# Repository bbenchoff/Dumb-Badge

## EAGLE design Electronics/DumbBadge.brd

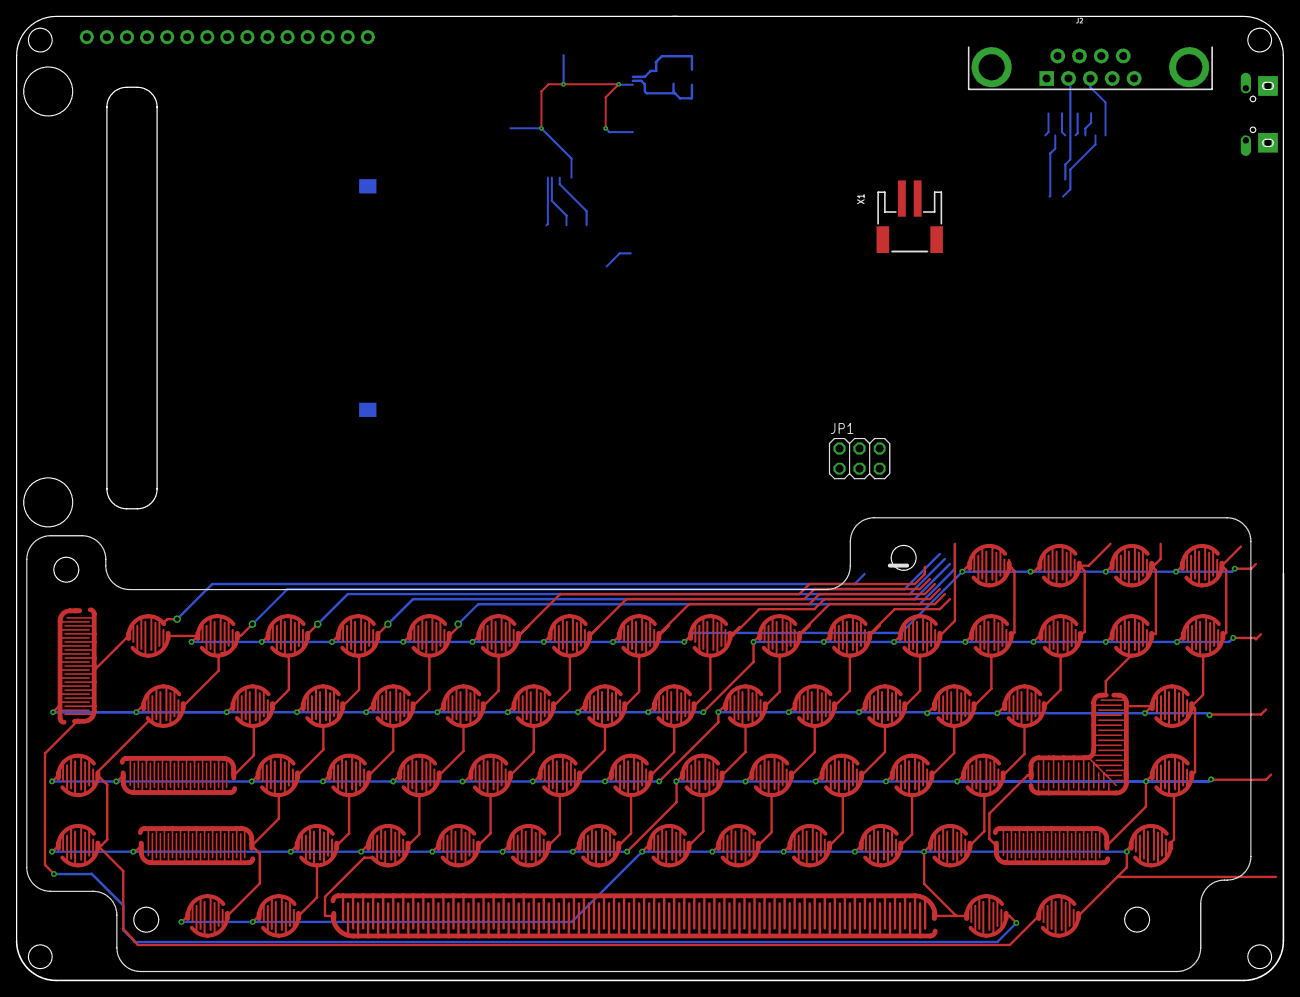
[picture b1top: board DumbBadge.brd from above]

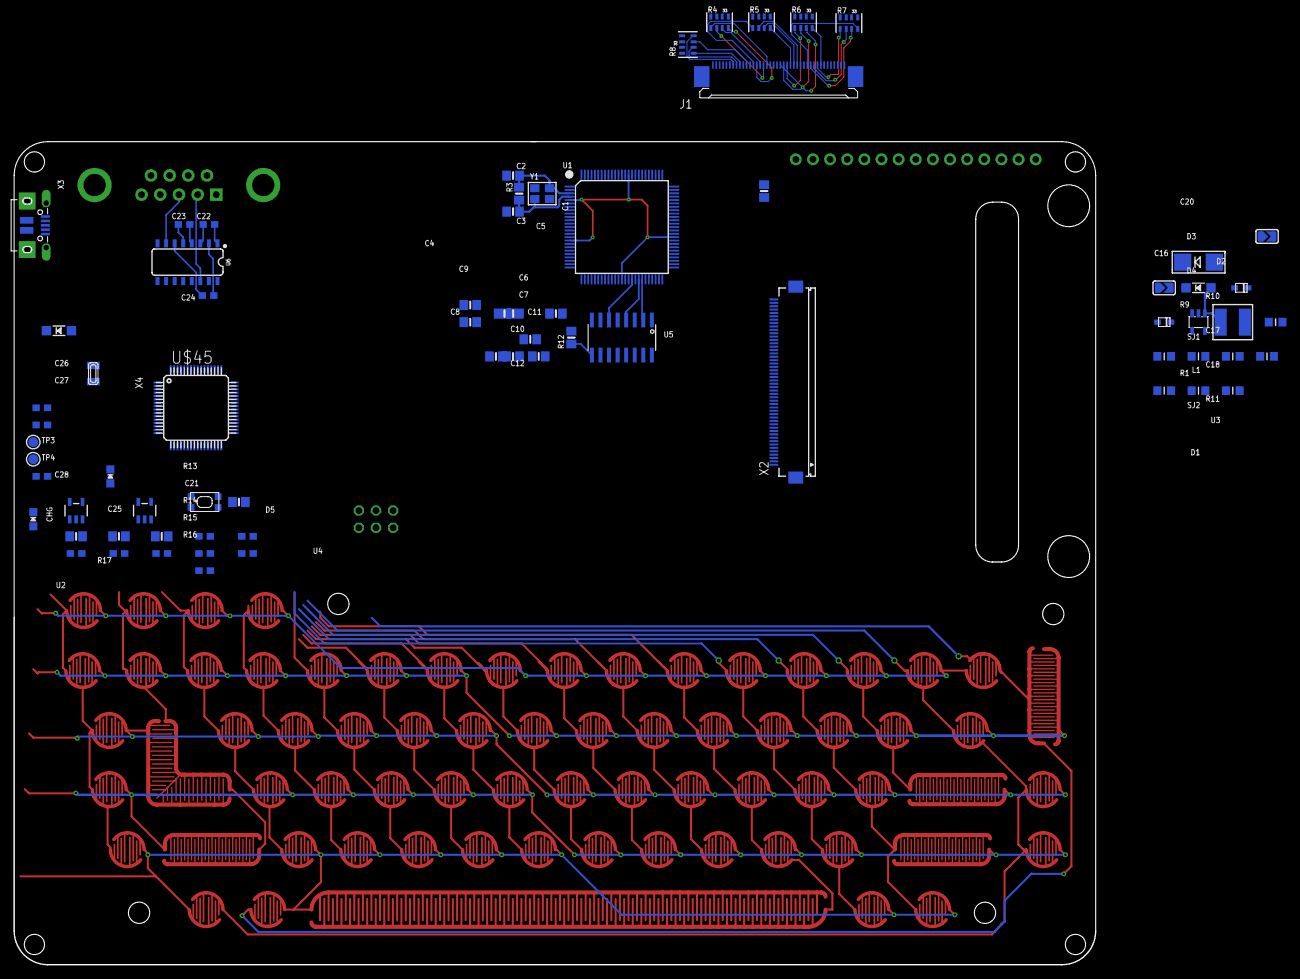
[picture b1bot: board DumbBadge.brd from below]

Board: 2 copper layers, 160.3 x 122.0 mm, 143 parts (70 on the bottom side), 115 nets.

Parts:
C1, C4, C5, C6, C7, C8, C9, C10, C11, C12: 0.1uF; 0805-NO
C2, C3: 20pF; 0805-NO
C13, C15, C21: 10µF; 0805-NO
C14, C19, C28: 1uF; 0603-NO
C16: 10uF; _0805MP
C17, C20: 1uF; _0805MP
C18: 0.1uF; _0805MP
C22, C23, C24: 0.1uF; 0603-NO
C25: 10uF; 0805-NO
C26, C27: 22pF; 0603-NO
CHG: ORANGE; CHIPLED_0805_NOOUTLINE
D1: MM3Z24VT1G; SMADIODE
D2: MBR0540; SOD-123
D3, D4: 1N4148; SOD-323F
D5: MBR120; SOD-123
J1: 40PINFPCM4-1734839-0; 4-1734839-0
J2: DB9
JP1: 2X03
JP2: Breakout; 1X15-CB
K-1, K-2, K-5: 1U_PAD; SILICONE_SWITCH
K_0, K_3, K_4, K_6, K_7, K_8, K_9: 1U_PAD; SILICONE_SWITCH
K_<: 1U_PAD; SILICONE_SWITCH
K_>: 1U_PAD; SILICONE_SWITCH
K_?: 1U_PAD; SILICONE_SWITCH
K_A: 1U_PAD; SILICONE_SWITCH
K_B: 1U_PAD; SILICONE_SWITCH
K_BACK: 1U_PAD; SILICONE_SWITCH
K_BREAK: 1U_PAD; SILICONE_SWITCH
K_C: 1U_PAD; SILICONE_SWITCH
K_CAPS: 1U_PAD; SILICONE_SWITCH
K_CONTROL: 2U_PAD; SILICONE_SWITCH_2U
K_D: 1U_PAD; SILICONE_SWITCH
K_DEL: 1U_PAD; SILICONE_SWITCH
K_DOWN: 1U_PAD; SILICONE_SWITCH
K_E: 1U_PAD; SILICONE_SWITCH
K_ESC: 1U_PAD; SILICONE_SWITCH
K_F: 1U_PAD; SILICONE_SWITCH
K_G: 1U_PAD; SILICONE_SWITCH
K_H: 1U_PAD; SILICONE_SWITCH
K_I: 1U_PAD; SILICONE_SWITCH
K_J: 1U_PAD; SILICONE_SWITCH
K_K: 1U_PAD; SILICONE_SWITCH
K_L: 1U_PAD; SILICONE_SWITCH
K_LEFT: 1U_PAD; SILICONE_SWITCH
K_LEFTALT: 1U_PAD; SILICONE_SWITCH
K_LEFTMETA: 1U_PAD; SILICONE_SWITCH
K_LINE: 1U_PAD; SILICONE_SWITCH
K_LSHIFT: 2U_PAD; SILICONE_SWITCH_2U
K_M: 1U_PAD; SILICONE_SWITCH
K_N: 1U_PAD; SILICONE_SWITCH
K_NOSCL: 1U_PAD; SILICONE_SWITCH
K_O: 1U_PAD; SILICONE_SWITCH
K_P: 1U_PAD; SILICONE_SWITCH
K_PIPE: 1U_PAD; SILICONE_SWITCH
K_PLUS: 1U_PAD; SILICONE_SWITCH
K_Q: 1U_PAD; SILICONE_SWITCH
K_QUOTE: 1U_PAD; SILICONE_SWITCH
K_R: 1U_PAD; SILICONE_SWITCH
K_RETURN: RETURN_PAD; SILICONE_RETURN
K_RIGHT: 1U_PAD; SILICONE_SWITCH
K_RIGHTALT: 1U_PAD; SILICONE_SWITCH
K_RIGHTMETA: 1U_PAD; SILICONE_SWITCH
K_RSHIFT: 2U_PAD; SILICONE_SWITCH_2U
K_S: 1U_PAD; SILICONE_SWITCH
K_SEMI: 1U_PAD; SILICONE_SWITCH
K_SETUP: 2U_PAD; SILICONE_SWITCH_2U
K_SPACE: SPACE_PAD; SILICONE_SPACE
K_T: 1U_PAD; SILICONE_SWITCH
K_TAB: 1U_PAD; SILICONE_SWITCH
K_TILDE: 1U_PAD; SILICONE_SWITCH
K_U: 1U_PAD; SILICONE_SWITCH
K_UP: 1U_PAD; SILICONE_SWITCH
K_USCORE: 1U_PAD; SILICONE_SWITCH
K_V: 1U_PAD; SILICONE_SWITCH
K_W: 1U_PAD; SILICONE_SWITCH
K_X: 1U_PAD; SILICONE_SWITCH
K_Y: 1U_PAD; SILICONE_SWITCH
K_Z: 1U_PAD; SILICONE_SWITCH
K_{: 1U_PAD; SILICONE_SWITCH
K_}: 1U_PAD; SILICONE_SWITCH
L: RED; CHIPLED_0805_NOOUTLINE
L1: 6.8uH large inductor; INDUCTOR_5X5MM_NR5040_NOTHERMALS
R1: 3Ω; _0805MP
R2: 2.2K; 0603-NO
R3: 1M; 0805-NO
R4, R5, R6, R7, R8: 33; RESPACK_4X0603
R9, R10: 12Ω; _0805MP
R11: 10K; _0805MP
R12: 10K; 0805-NO
R13: 1K; 0603-NO
R14: 10K\; 0603-NO
R15, R17: 100k; 0603-NO
R16: 100K; 0603-NO
SJ1: +25mA; SOLDERJUMPER_ARROW_NOPASTE
SJ2: +100mA; SOLDERJUMPER_ARROW_NOPASTE
SW1: SPST_TACT-KMR2; KMR2
TP3, TP4: TESTPOINT_ROUND_1.5MM
U1: RA8875; LQFP100
U2: SPX3819-3.3; SOT23-5
U3: FAN5333BSX; SOT23-5@1
U4: MCP73831T-2ACI/OT; SOT23-5
U5: 74HC4050; SOIC16
U6: MAX3232; SO16
U$45: ATSAMD21J18A-AUT; TQFP64-10X10
X1: JSTPH; JSTPH2
X2: FH12-50S-0.5SH
X3: microUSB; 4UCONN_20329_V2
X4: 32.768; XTAL3215
Y1: 20MHz; CRYSTAL_3.2X2.5

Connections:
1: X2.13, X2.14, X2.15, X2.16, X2.17, X2.18, X2.19, X2.20, X2.21, X2.22, X2.23, X2.24, X2.25, X2.26, X2.27, X2.28, X2.29, X2.30, X2.31, X2.32, X2.33, X2.34, X2.35, X2.36
1.5V: C8.1, C9.1, C10.1, C12.1, U1.5, U1.17, U1.38, U1.60, U1.86
!RESET: SW1.1, SW1.3, U$45.52
+3V3: C4.1, C5.1, C6.1, C7.1, C11.1, C14.1, C15.1, C25.1, J1.4, JP2.13, R12.2, U1.2, U1.13, U1.25, U1.27, U1.40, U1.62, U1.76, U1.77, U1.78, U1.79, U1.80, U1.87, U2.5, U5.1, U$45.8, U$45.21, U$45.34, U$45.48, U$45.56
+24V: C17.1, C20.1, D1.C, D2.C, J1.2
AREF: C19.1, U$45.4
B3: J1.24, R4.5
B4: J1.25, R4.6
B5: J1.26, R4.7
B6: J1.27, R4.8
B7: J1.28, R5.5
CS: JP2.8, X2.42
D9: R15.2, R16.1, U$45.16
D13: R2.1, U$45.36
D+: U$45.46, X3.D+
D-: U$45.45, X3.D-
DE: J1.34, R8.8, X2.12
EN: R17.2, U2.3
G2: J1.15, R5.6
G3: J1.16, R5.7
G4: J1.17, R5.8
G5: J1.18, R6.5
G6: J1.19, R6.6
G7: J1.20, R6.7
GND: C1.2, C2.1, C3.1, C4.2, C5.2, C6.2, C7.2, C8.2, C9.2, C10.2, C11.2, C12.2, C13.2, C14.2, C15.2, C16.2, C17.2, C18.2, C19.2, C20.2, C21.2, C25.2, C26.2, C27.2, C28.2, J1.3, J1.5, J1.6, J1.7, J1.13, J1.14, J1.21, J1.22, J1.23, J1.29, J1.36, J2.5, JP2.14, L.C, R10.1, R14.2, R16.2, SJ1.1, SJ2.1, SW1.2, SW1.4, U1.1, U1.6, U1.10, U1.11, U1.12, U1.16, U1.23, U1.24, U1.26, U1.28, U1.33, U1.34, U1.35, U1.36, U1.37, U1.39, U1.45, U1.61, U1.70, U1.81, U1.85, U2.2, U3.2, U4.2, U5.8, U$45.7, U$45.22, U$45.33, U$45.47, U$45.54, X1.1, X2.45, X2.50, X3.BASE@1, X3.BASE@2, X3.GND, X3.SPRT@1, X3.SPRT@2, X3.SPRT@3, X3.SPRT@4
HSYNC: J1.32, R8.5, X2.10
INT: JP2.5, U1.8
KEYCOLUMN0: K_ESC.P$2, K_RIGHTALT.P$2, K_SETUP.P$2
KEYCOLUMN1: K-1.P$2, K_CAPS.P$2, K_NOSCL.P$2, K_RIGHTMETA.P$2, K_TAB.P$2
KEYCOLUMN2: K-2.P$2, K_CONTROL.P$2, K_Q.P$2
KEYCOLUMN3: K_3.P$2, K_A.P$2, K_LEFTMETA.P$2, K_LSHIFT.P$2, K_W.P$2
KEYCOLUMN4: K_4.P$2, K_E.P$2, K_LEFTALT.P$2, K_S.P$2, K_Z.P$2
KEYCOLUMN5: K-5.P$2, K_D.P$2, K_R.P$2, K_SPACE.P$1, K_X.P$2
KEYCOLUMN6: K_6.P$2, K_C.P$2, K_F.P$2, K_T.P$2
KEYCOLUMN7: K_7.P$2, K_G.P$2, K_V.P$2, K_Y.P$2
KEYCOLUMN8: K_8.P$2, K_B.P$2, K_H.P$2, K_U.P$2
KEYCOLUMN9: K_9.P$2, K_I.P$2, K_J.P$2, K_N.P$2
KEYCOLUMN10: K_0.P$2, K_K.P$2, K_M.P$2, K_O.P$2
KEYCOLUMN11: K_<.P$2, K_L.P$2, K_P.P$2, K_USCORE.P$2
KEYCOLUMN12: K_>.P$2, K_LEFT.P$2, K_PLUS.P$2, K_SEMI.P$2, K_{.P$2
KEYCOLUMN13: K_?.P$2, K_DOWN.P$2, K_QUOTE.P$2, K_TILDE.P$2, K_}.P$2
KEYCOLUMN14: K_BACK.P$2, K_RETURN.P$1, K_RSHIFT.P$1, K_UP.P$2
KEYCOLUMN15: K_BREAK.P$2, K_DEL.P$2, K_LINE.P$2, K_PIPE.P$2, K_RIGHT.P$2
KEYROW0: K-1.P$1, K-2.P$1, K-5.P$1, K_3.P$1, K_4.P$1, K_6.P$1, K_7.P$1, K_8.P$1, K_DOWN.P$1, K_ESC.P$1, K_LEFT.P$1, K_RIGHT.P$1, K_UP.P$1
KEYROW1: K_0.P$1, K_9.P$1, K_BACK.P$1, K_BREAK.P$1, K_E.P$1, K_PLUS.P$1, K_Q.P$1, K_R.P$1, K_SETUP.P$1, K_T.P$1, K_TAB.P$1, K_TILDE.P$1, K_U.P$1, K_USCORE.P$1, K_W.P$1, K_Y.P$1
KEYROW2: K_A.P$1, K_CAPS.P$1, K_CONTROL.P$1, K_D.P$1, K_DEL.P$1, K_F.P$1, K_G.P$1, K_H.P$1, K_I.P$1, K_O.P$1, K_P.P$1, K_RETURN.P$2, K_S.P$1, K_{.P$1, K_}.P$1
KEYROW3: K_B.P$1, K_C.P$1, K_J.P$1, K_K.P$1, K_L.P$1, K_LSHIFT.P$1, K_NOSCL.P$1, K_PIPE.P$1, K_QUOTE.P$1, K_RSHIFT.P$2, K_SEMI.P$1, K_V.P$1, K_X.P$1, K_Z.P$1
KEYROW4: K_<.P$1, K_>.P$1, K_?.P$1, K_LEFTALT.P$1, K_LEFTMETA.P$1, K_LINE.P$1, K_M.P$1, K_N.P$1, K_RIGHTALT.P$1, K_RIGHTMETA.P$1, K_SPACE.P$2
LEDK: C18.1, D1.A, J1.1, R1.2, R9.2, R10.2, U3.3
MISO: JP2.10, U1.42, U$45.29
MOSI: JP2.9, U$45.23
MOSI_3V: U1.43, U5.4
unnamed: D2.A, L1.P$2, U3.1
unnamed: R4.4, U1.51
unnamed: R9.1, SJ1.2
unnamed: R4.3, U1.52
unnamed: R1.1, SJ2.2
unnamed: R4.2, U1.53
unnamed: R4.1, U1.54
unnamed: R5.4, U1.55
unnamed: R5.3, U1.56
unnamed: R5.2, U1.57
unnamed: R5.1, U1.58
unnamed: R6.4, U1.59
unnamed: R6.3, U1.63
unnamed: R6.2, U1.64
unnamed: R6.1, U1.65
unnamed: R7.4, U1.66
unnamed: R7.3, U1.67
unnamed: R7.2, U1.68
unnamed: R7.1, U1.69
unnamed: R8.1, U1.50
unnamed: R8.2, U1.49
unnamed: R8.3, U1.48
unnamed: R8.4, U1.47
unnamed: C1.1, U1.71
unnamed: C2.2, R3.2, U1.3, Y1.2
unnamed: C3.2, R3.1, U1.4, Y1.1
unnamed: L.A, R2.2
unnamed: CHG.C, R13.1
unnamed: R13.2, U4.1
unnamed: R14.1, U4.5
unnamed: J2.2, U6.14
unnamed: J2.3, U6.7
unnamed: C26.1, U$45.1, X4.P$1
unnamed: C27.1, U$45.2, X4.P$2
unnamed: C22.2, U6.3
unnamed: C22.1, U6.1
unnamed: C23.1, U6.4
unnamed: C23.2, U6.5
unnamed: C24.1, U6.2
unnamed: C24.2, U6.6
ON/OFF: J1.31, U1.46
PIXCLK: J1.30, R8.7
PWM0: D3.C, U1.14
R3: J1.8, R6.8
R4: J1.9, R7.5
R5: J1.10, R7.6
R6: J1.11, R7.7
R7: J1.12, R7.8
RESET: JP2.7, X2.8
RESET_3V: U1.9, U5.10
RESET_BUFFER: R12.1, U5.9
SCK: JP2.11, U$45.24
SHDN: D3.A, D4.A, R11.1, U3.4
SPI_CLK_3V: U1.44, U5.2
SPI_CS_3V: U1.41, U5.6
SWCLK: TP3.P$1, U$45.57
SWDIO: TP4.P$1, U$45.58
VBAT: C21.1, D5.A, R15.1, U4.3, X1.2
VBUS: C13.1, CHG.A, D5.C, R17.1, U2.1, U4.4, X3.VBUS
VDDCORE2: C28.1, U$45.55
VIN: C16.1, JP2.15, L1.P$1, R11.2, U3.5
VSYNC: J1.33, R8.6, X2.9
WAIT: JP2.6, U1.7

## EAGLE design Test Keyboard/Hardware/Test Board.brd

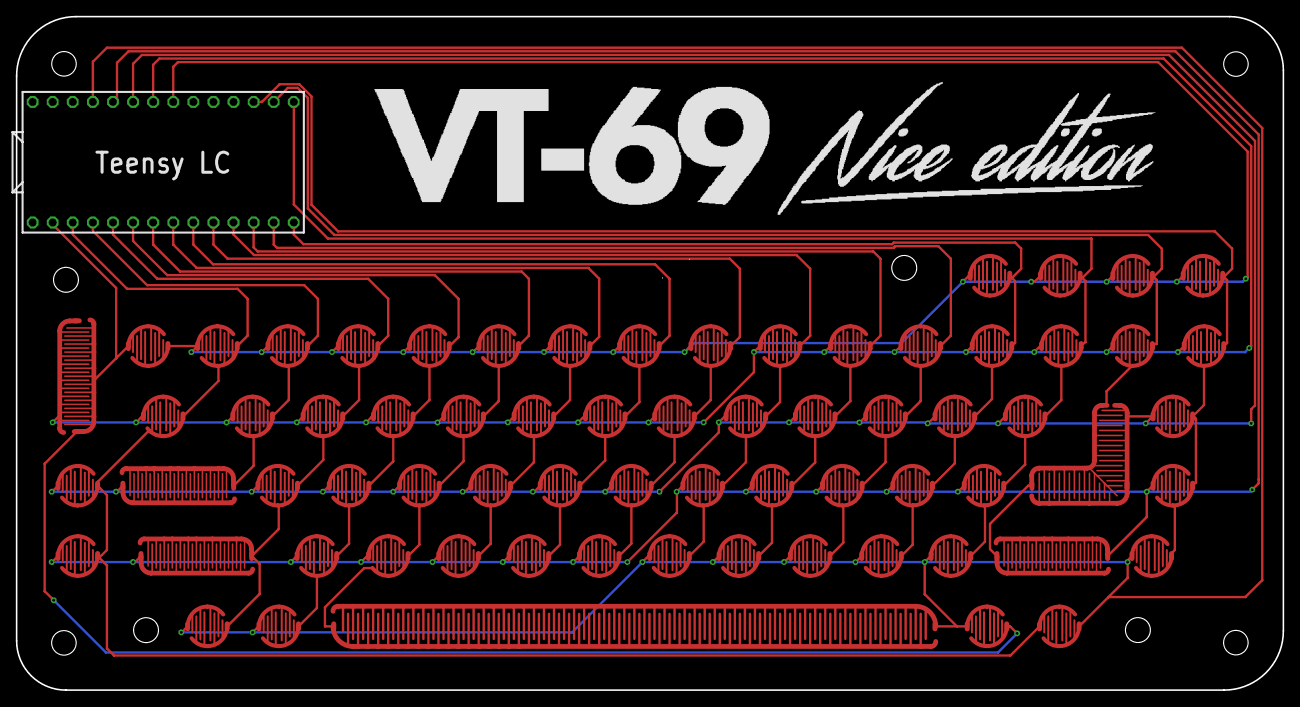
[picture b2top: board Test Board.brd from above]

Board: 2 copper layers, 160.1 x 85.1 mm, 70 parts (0 on the bottom side), 21 nets.

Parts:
K-1, K-2, K-5: 1U_PAD; SILICONE_SWITCH
K_0, K_3, K_4, K_6, K_7, K_8, K_9: 1U_PAD; SILICONE_SWITCH
K_<: 1U_PAD; SILICONE_SWITCH
K_>: 1U_PAD; SILICONE_SWITCH
K_?: 1U_PAD; SILICONE_SWITCH
K_A: 1U_PAD; SILICONE_SWITCH
K_B: 1U_PAD; SILICONE_SWITCH
K_BACK: 1U_PAD; SILICONE_SWITCH
K_BREAK: 1U_PAD; SILICONE_SWITCH
K_C: 1U_PAD; SILICONE_SWITCH
K_CAPS: 1U_PAD; SILICONE_SWITCH
K_CONTROL: 2U_PAD; SILICONE_SWITCH_2U
K_D: 1U_PAD; SILICONE_SWITCH
K_DEL: 1U_PAD; SILICONE_SWITCH
K_DOWN: 1U_PAD; SILICONE_SWITCH
K_E: 1U_PAD; SILICONE_SWITCH
K_ESC: 1U_PAD; SILICONE_SWITCH
K_F: 1U_PAD; SILICONE_SWITCH
K_G: 1U_PAD; SILICONE_SWITCH
K_H: 1U_PAD; SILICONE_SWITCH
K_I: 1U_PAD; SILICONE_SWITCH
K_J: 1U_PAD; SILICONE_SWITCH
K_K: 1U_PAD; SILICONE_SWITCH
K_L: 1U_PAD; SILICONE_SWITCH
K_LEFT: 1U_PAD; SILICONE_SWITCH
K_LEFTALT: 1U_PAD; SILICONE_SWITCH
K_LEFTMETA: 1U_PAD; SILICONE_SWITCH
K_LINE: 1U_PAD; SILICONE_SWITCH
K_LSHIFT: 2U_PAD; SILICONE_SWITCH_2U
K_M: 1U_PAD; SILICONE_SWITCH
K_N: 1U_PAD; SILICONE_SWITCH
K_NOSCL: 1U_PAD; SILICONE_SWITCH
K_O: 1U_PAD; SILICONE_SWITCH
K_P: 1U_PAD; SILICONE_SWITCH
K_PIPE: 1U_PAD; SILICONE_SWITCH
K_PLUS: 1U_PAD; SILICONE_SWITCH
K_Q: 1U_PAD; SILICONE_SWITCH
K_QUOTE: 1U_PAD; SILICONE_SWITCH
K_R: 1U_PAD; SILICONE_SWITCH
K_RETURN: RETURN_PAD; SILICONE_RETURN
K_RIGHT: 1U_PAD; SILICONE_SWITCH
K_RIGHTALT: 1U_PAD; SILICONE_SWITCH
K_RIGHTMETA: 1U_PAD; SILICONE_SWITCH
K_RSHIFT: 2U_PAD; SILICONE_SWITCH_2U
K_S: 1U_PAD; SILICONE_SWITCH
K_SEMI: 1U_PAD; SILICONE_SWITCH
K_SETUP: 2U_PAD; SILICONE_SWITCH_2U
K_SPACE: SPACE_PAD; SILICONE_SPACE
K_T: 1U_PAD; SILICONE_SWITCH
K_TAB: 1U_PAD; SILICONE_SWITCH
K_TILDE: 1U_PAD; SILICONE_SWITCH
K_U: 1U_PAD; SILICONE_SWITCH
K_UP: 1U_PAD; SILICONE_SWITCH
K_USCORE: 1U_PAD; SILICONE_SWITCH
K_V: 1U_PAD; SILICONE_SWITCH
K_W: 1U_PAD; SILICONE_SWITCH
K_X: 1U_PAD; SILICONE_SWITCH
K_Y: 1U_PAD; SILICONE_SWITCH
K_Z: 1U_PAD; SILICONE_SWITCH
K_{: 1U_PAD; SILICONE_SWITCH
K_}: 1U_PAD; SILICONE_SWITCH
U$1: TEENSYLC; 2X14

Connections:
KEYCOLUMN0: K_ESC.P$2, K_RIGHTALT.P$2, K_SETUP.P$2, U$1.0
KEYCOLUMN1: K-1.P$2, K_CAPS.P$2, K_NOSCL.P$2, K_RIGHTMETA.P$2, K_TAB.P$2, U$1.1
KEYCOLUMN2: K-2.P$2, K_CONTROL.P$2, K_Q.P$2, U$1.2
KEYCOLUMN3: K_3.P$2, K_A.P$2, K_LEFTMETA.P$2, K_LSHIFT.P$2, K_W.P$2, U$1.3
KEYCOLUMN4: K_4.P$2, K_E.P$2, K_LEFTALT.P$2, K_S.P$2, K_Z.P$2, U$1.4
KEYCOLUMN5: K-5.P$2, K_D.P$2, K_R.P$2, K_SPACE.P$1, K_X.P$2, U$1.5
KEYCOLUMN6: K_6.P$2, K_C.P$2, K_F.P$2, K_T.P$2, U$1.6
KEYCOLUMN7: K_7.P$2, K_G.P$2, K_V.P$2, K_Y.P$2, U$1.7
KEYCOLUMN8: K_8.P$2, K_B.P$2, K_H.P$2, K_U.P$2, U$1.8
KEYCOLUMN9: K_9.P$2, K_I.P$2, K_J.P$2, K_N.P$2, U$1.9
KEYCOLUMN10: K_0.P$2, K_K.P$2, K_M.P$2, K_O.P$2, U$1.10
KEYCOLUMN11: K_<.P$2, K_L.P$2, K_P.P$2, K_USCORE.P$2, U$1.11
KEYCOLUMN12: K_>.P$2, K_LEFT.P$2, K_PLUS.P$2, K_SEMI.P$2, K_{.P$2, U$1.12
KEYCOLUMN13: K_?.P$2, K_DOWN.P$2, K_QUOTE.P$2, K_TILDE.P$2, K_}.P$2, U$1.13
KEYCOLUMN14: K_BACK.P$2, K_RETURN.P$1, K_RSHIFT.P$1, K_UP.P$2, U$1.14
KEYCOLUMN15: K_BREAK.P$2, K_DEL.P$2, K_LINE.P$2, K_PIPE.P$2, K_RIGHT.P$2, U$1.15
KEYROW0: K-1.P$1, K-2.P$1, K-5.P$1, K_3.P$1, K_4.P$1, K_6.P$1, K_7.P$1, K_8.P$1, K_DOWN.P$1, K_ESC.P$1, K_LEFT.P$1, K_RIGHT.P$1, K_UP.P$1, U$1.19
KEYROW1: K_0.P$1, K_9.P$1, K_BACK.P$1, K_BREAK.P$1, K_E.P$1, K_PLUS.P$1, K_Q.P$1, K_R.P$1, K_SETUP.P$1, K_T.P$1, K_TAB.P$1, K_TILDE.P$1, K_U.P$1, K_USCORE.P$1, K_W.P$1, K_Y.P$1, U$1.20
KEYROW2: K_A.P$1, K_CAPS.P$1, K_CONTROL.P$1, K_D.P$1, K_DEL.P$1, K_F.P$1, K_G.P$1, K_H.P$1, K_I.P$1, K_O.P$1, K_P.P$1, K_RETURN.P$2, K_S.P$1, K_{.P$1, K_}.P$1, U$1.21
KEYROW3: K_B.P$1, K_C.P$1, K_J.P$1, K_K.P$1, K_L.P$1, K_LSHIFT.P$1, K_NOSCL.P$1, K_PIPE.P$1, K_QUOTE.P$1, K_RSHIFT.P$2, K_SEMI.P$1, K_V.P$1, K_X.P$1, K_Z.P$1, U$1.22
KEYROW4: K_<.P$1, K_>.P$1, K_?.P$1, K_LEFTALT.P$1, K_LEFTMETA.P$1, K_LINE.P$1, K_M.P$1, K_N.P$1, K_RIGHTALT.P$1, K_RIGHTMETA.P$1, K_SPACE.P$2, U$1.23

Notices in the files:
parts and their libraries:
microbuilder: This work is placed in the public domain, and may be freely used for commercial and non-commercial work with the following conditions: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
SparkFun-IC-Comms: Licensing: Creative Commons ShareAlike 4.0 International - https://creativecommons.org/licenses/by-sa/4.0
